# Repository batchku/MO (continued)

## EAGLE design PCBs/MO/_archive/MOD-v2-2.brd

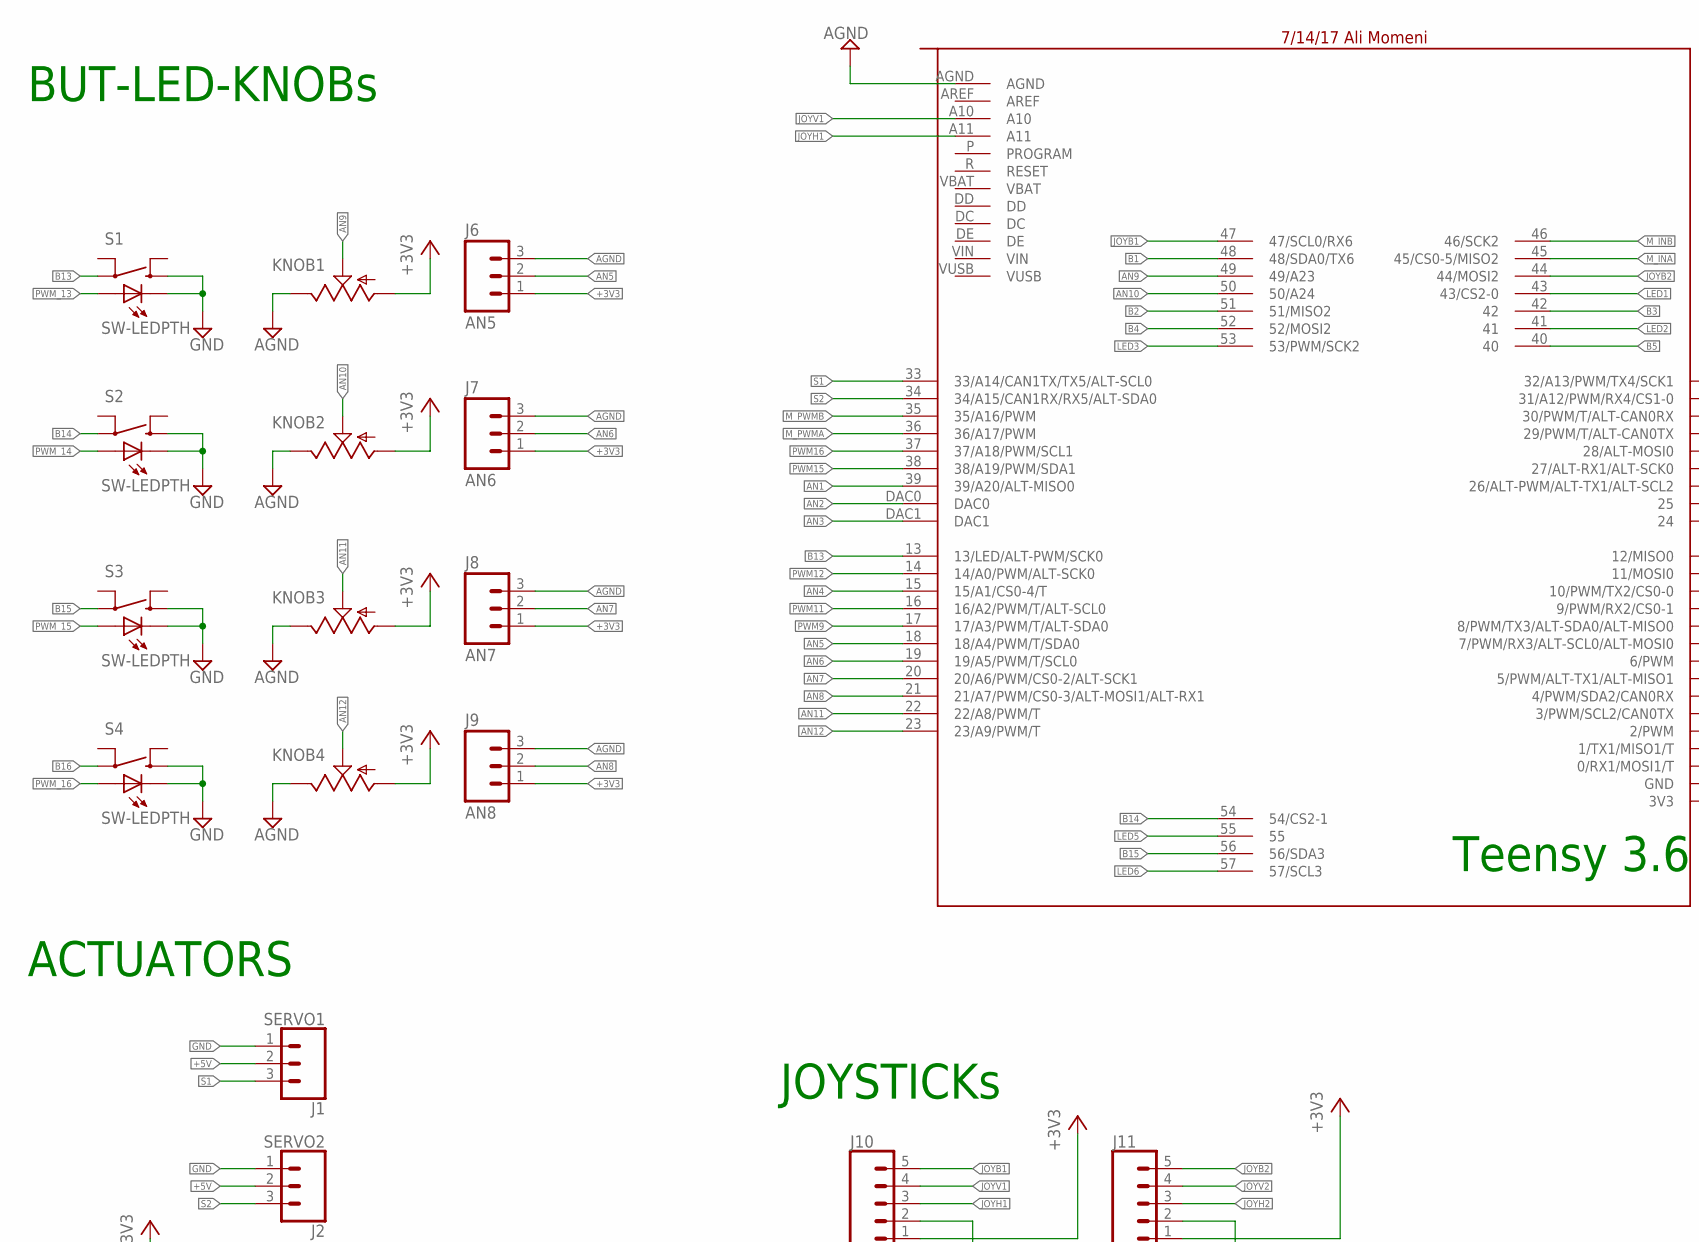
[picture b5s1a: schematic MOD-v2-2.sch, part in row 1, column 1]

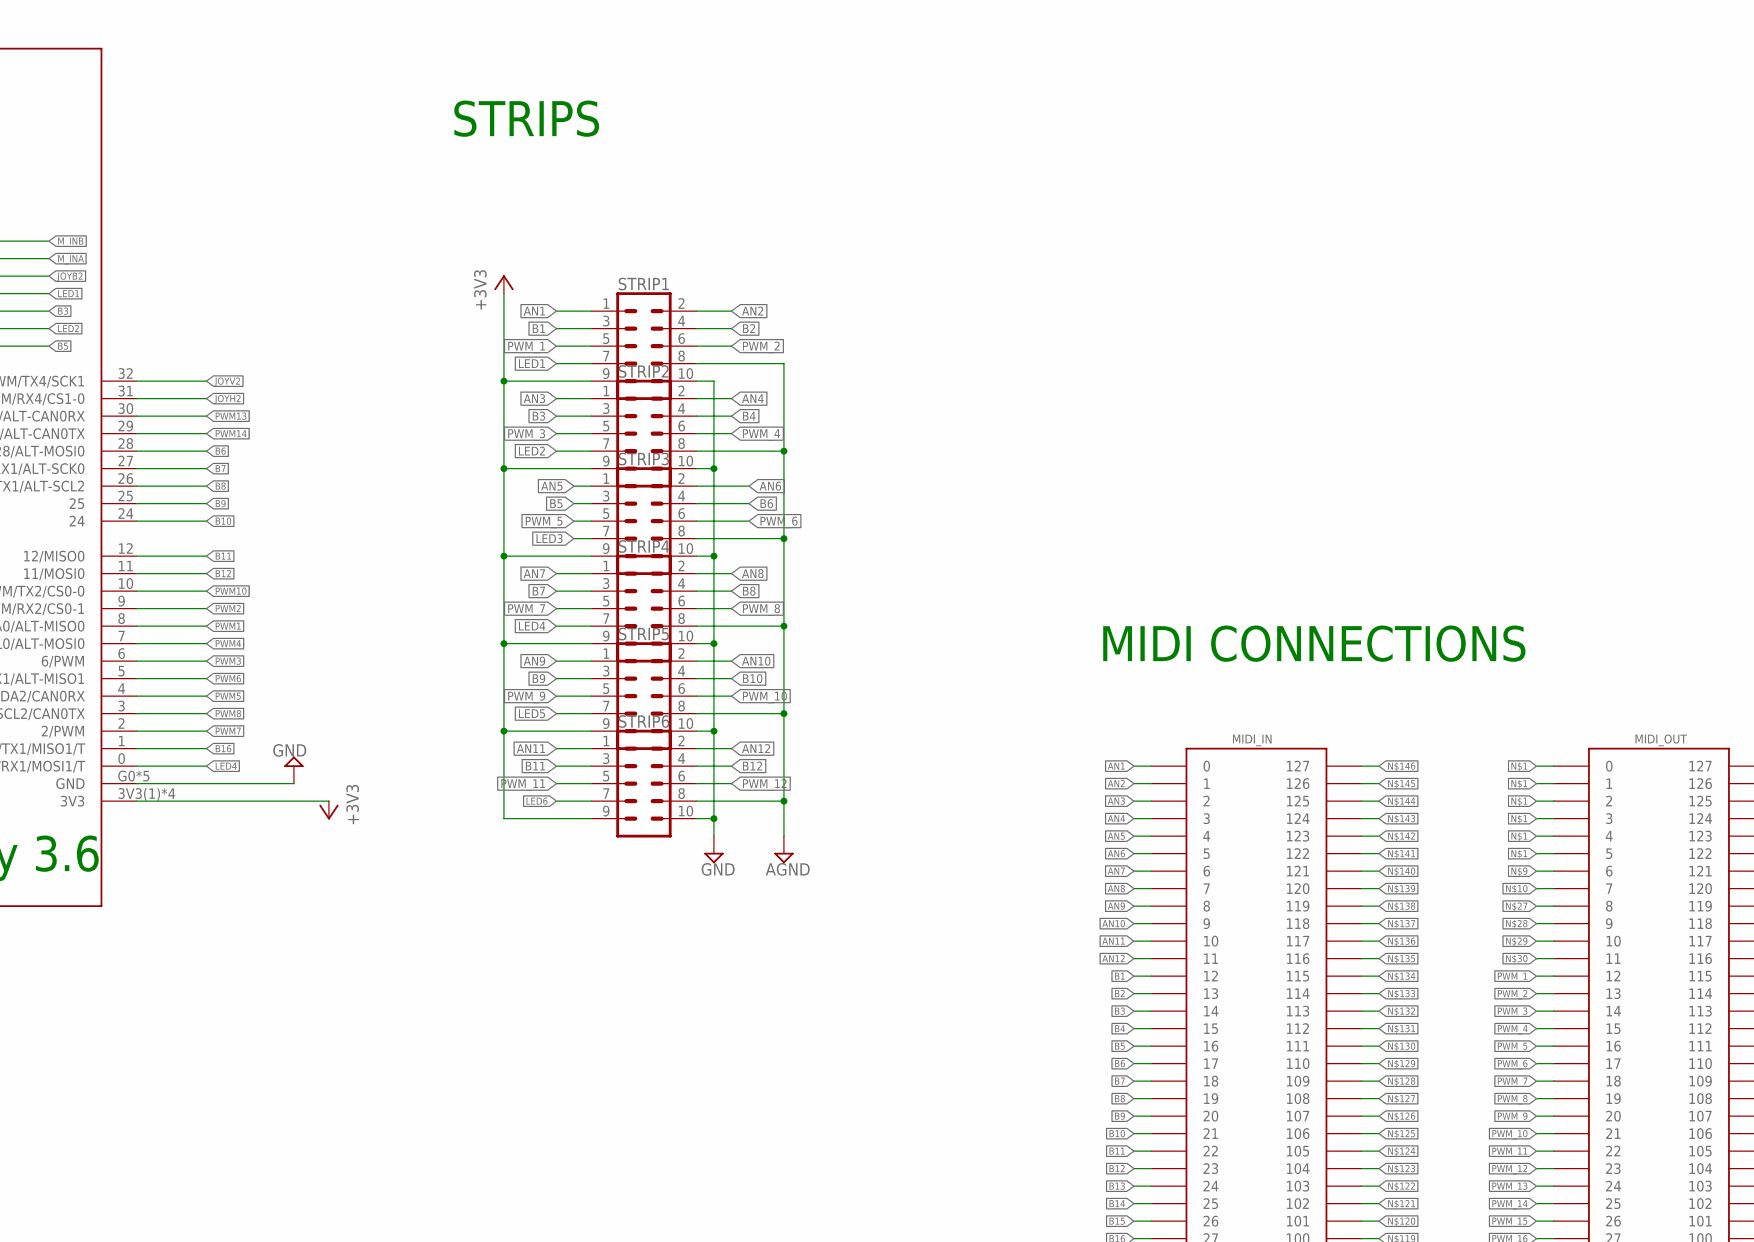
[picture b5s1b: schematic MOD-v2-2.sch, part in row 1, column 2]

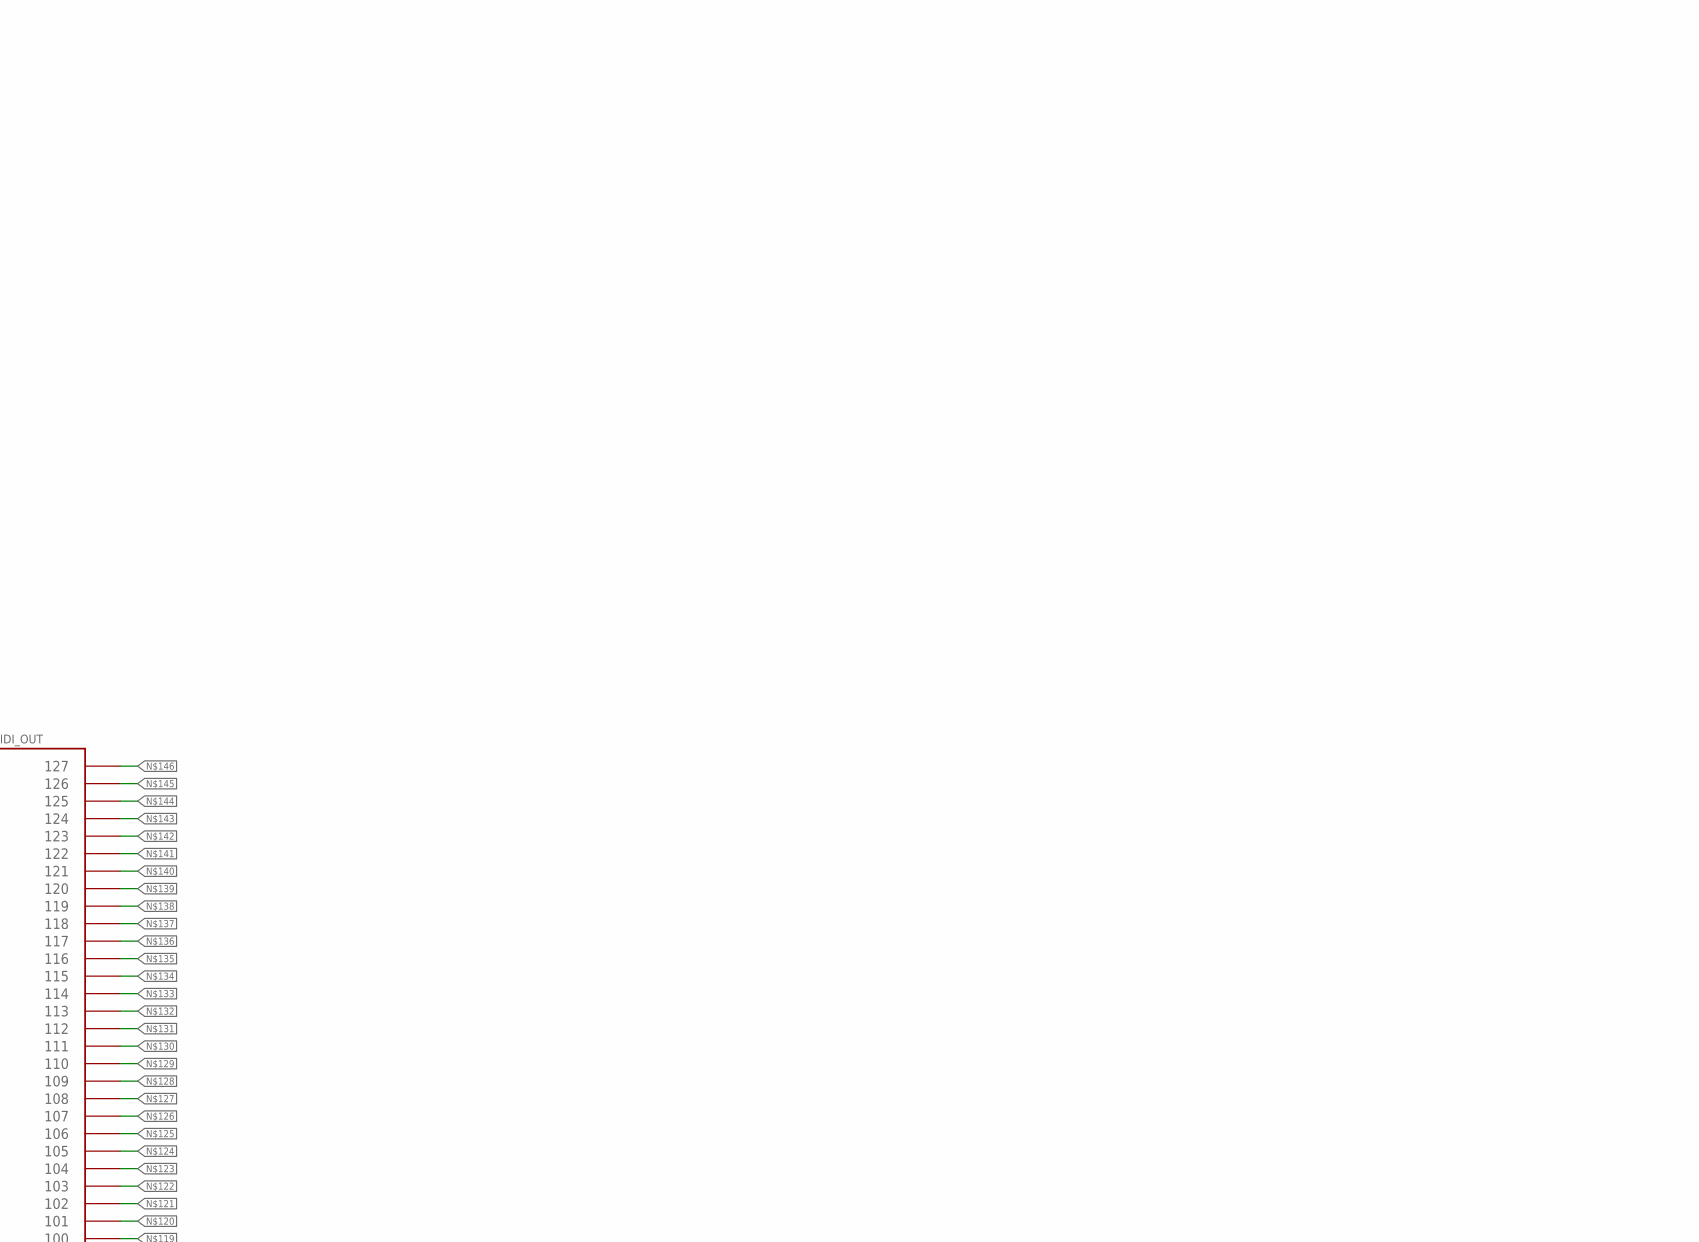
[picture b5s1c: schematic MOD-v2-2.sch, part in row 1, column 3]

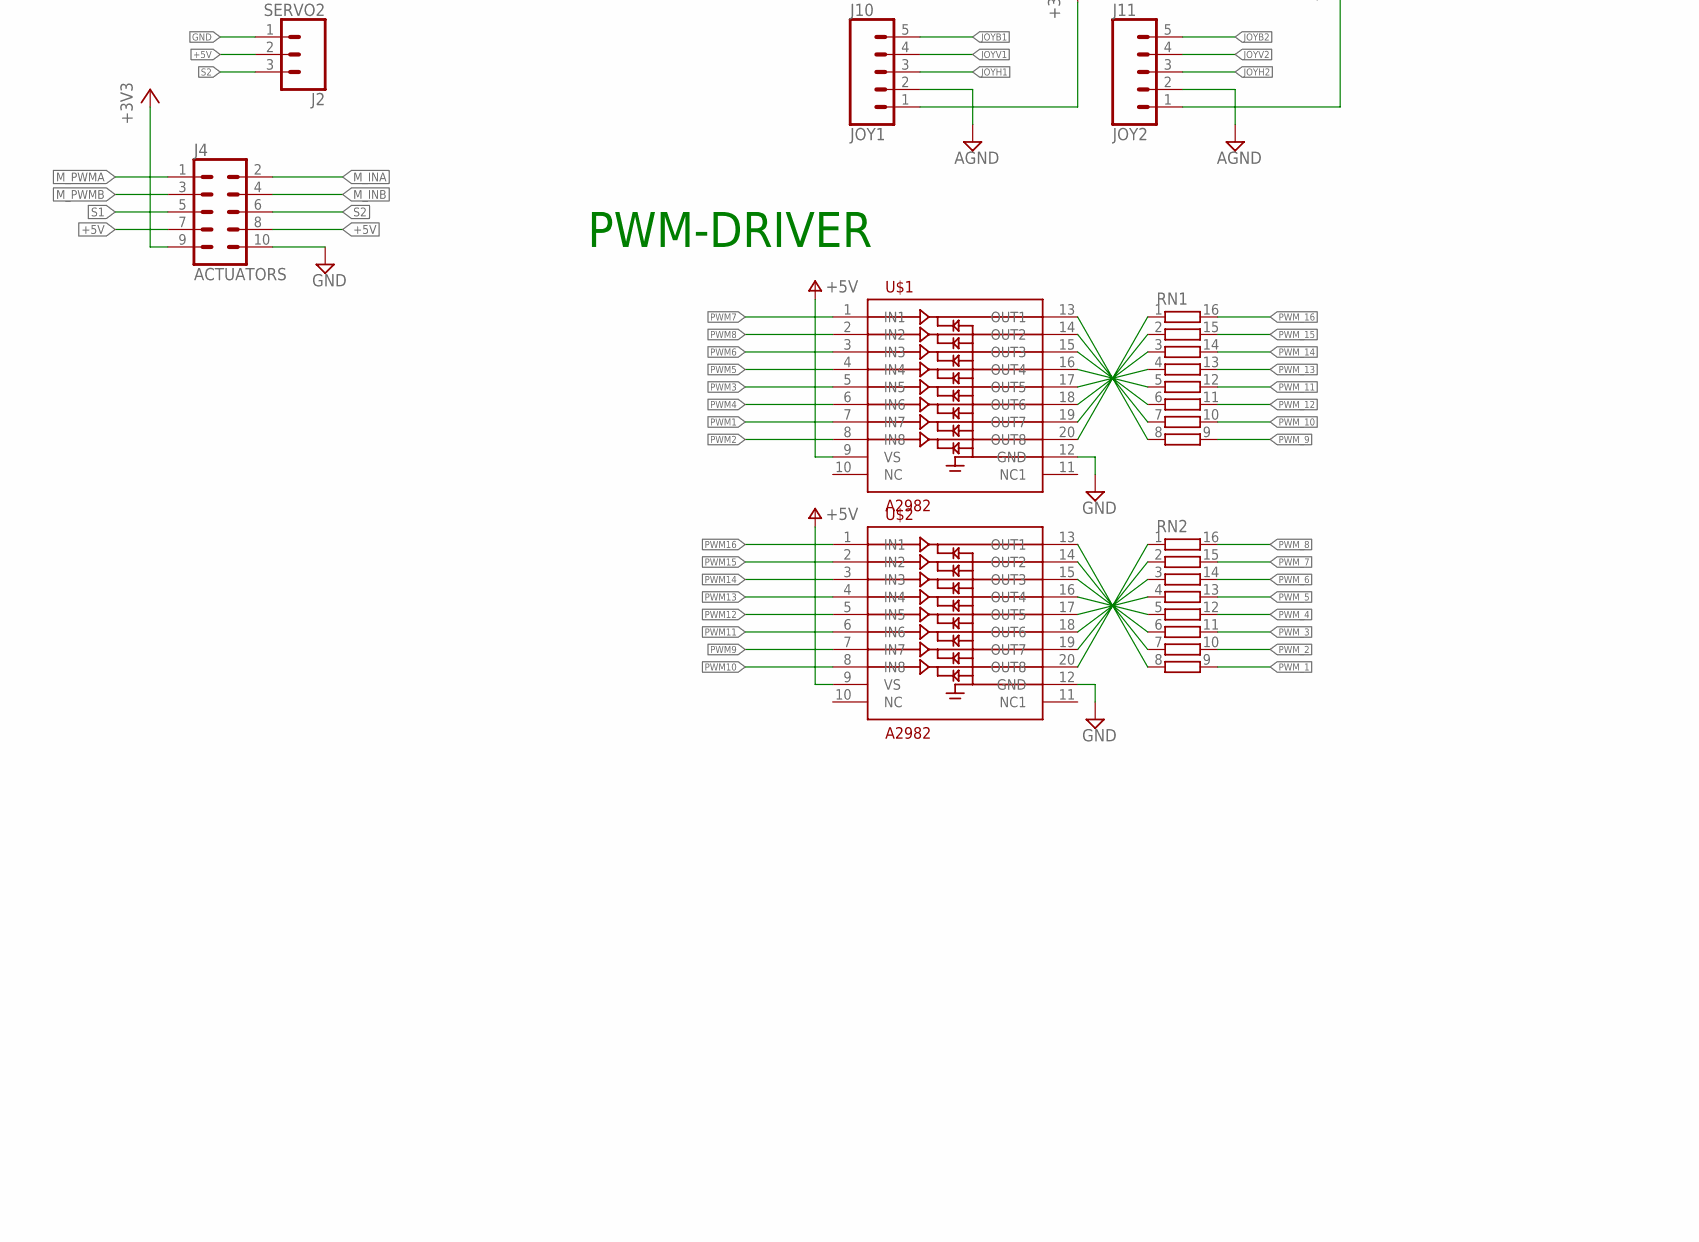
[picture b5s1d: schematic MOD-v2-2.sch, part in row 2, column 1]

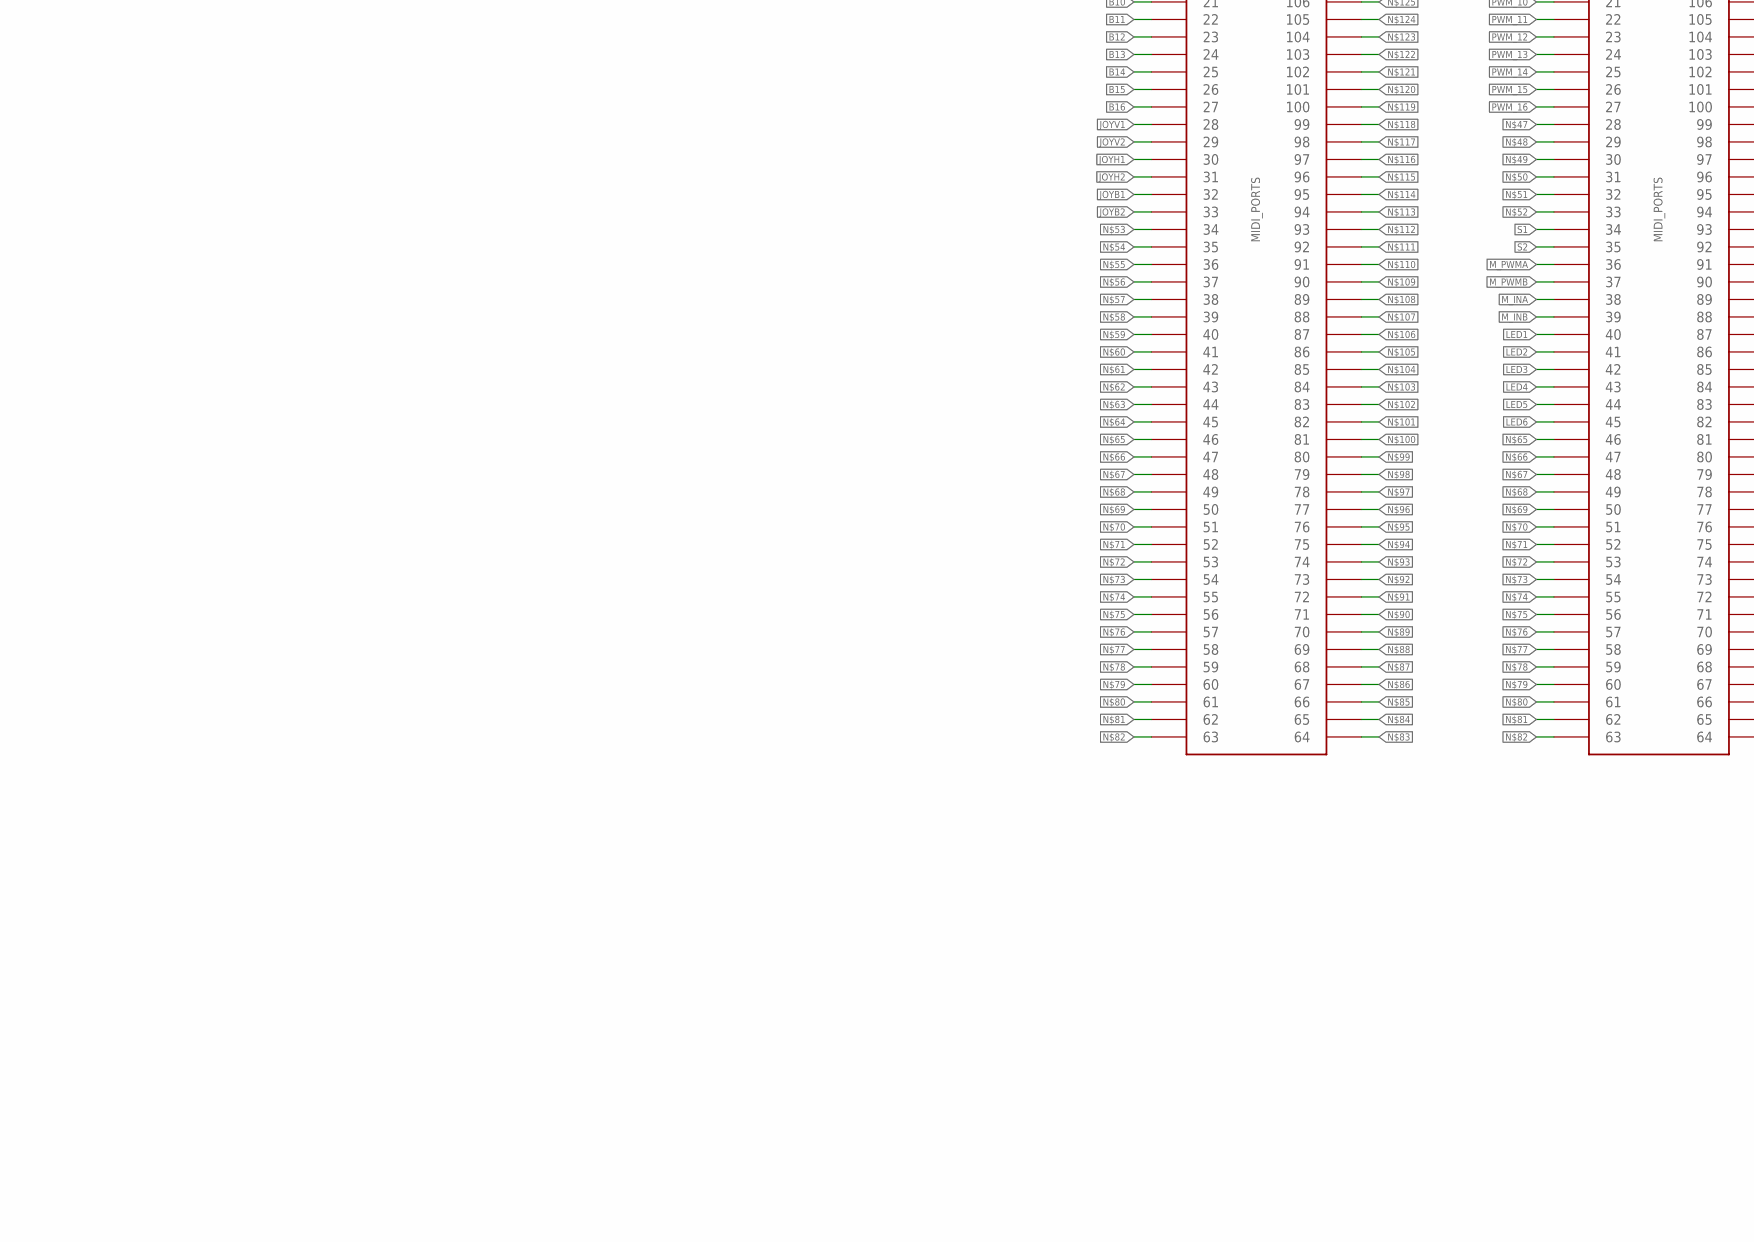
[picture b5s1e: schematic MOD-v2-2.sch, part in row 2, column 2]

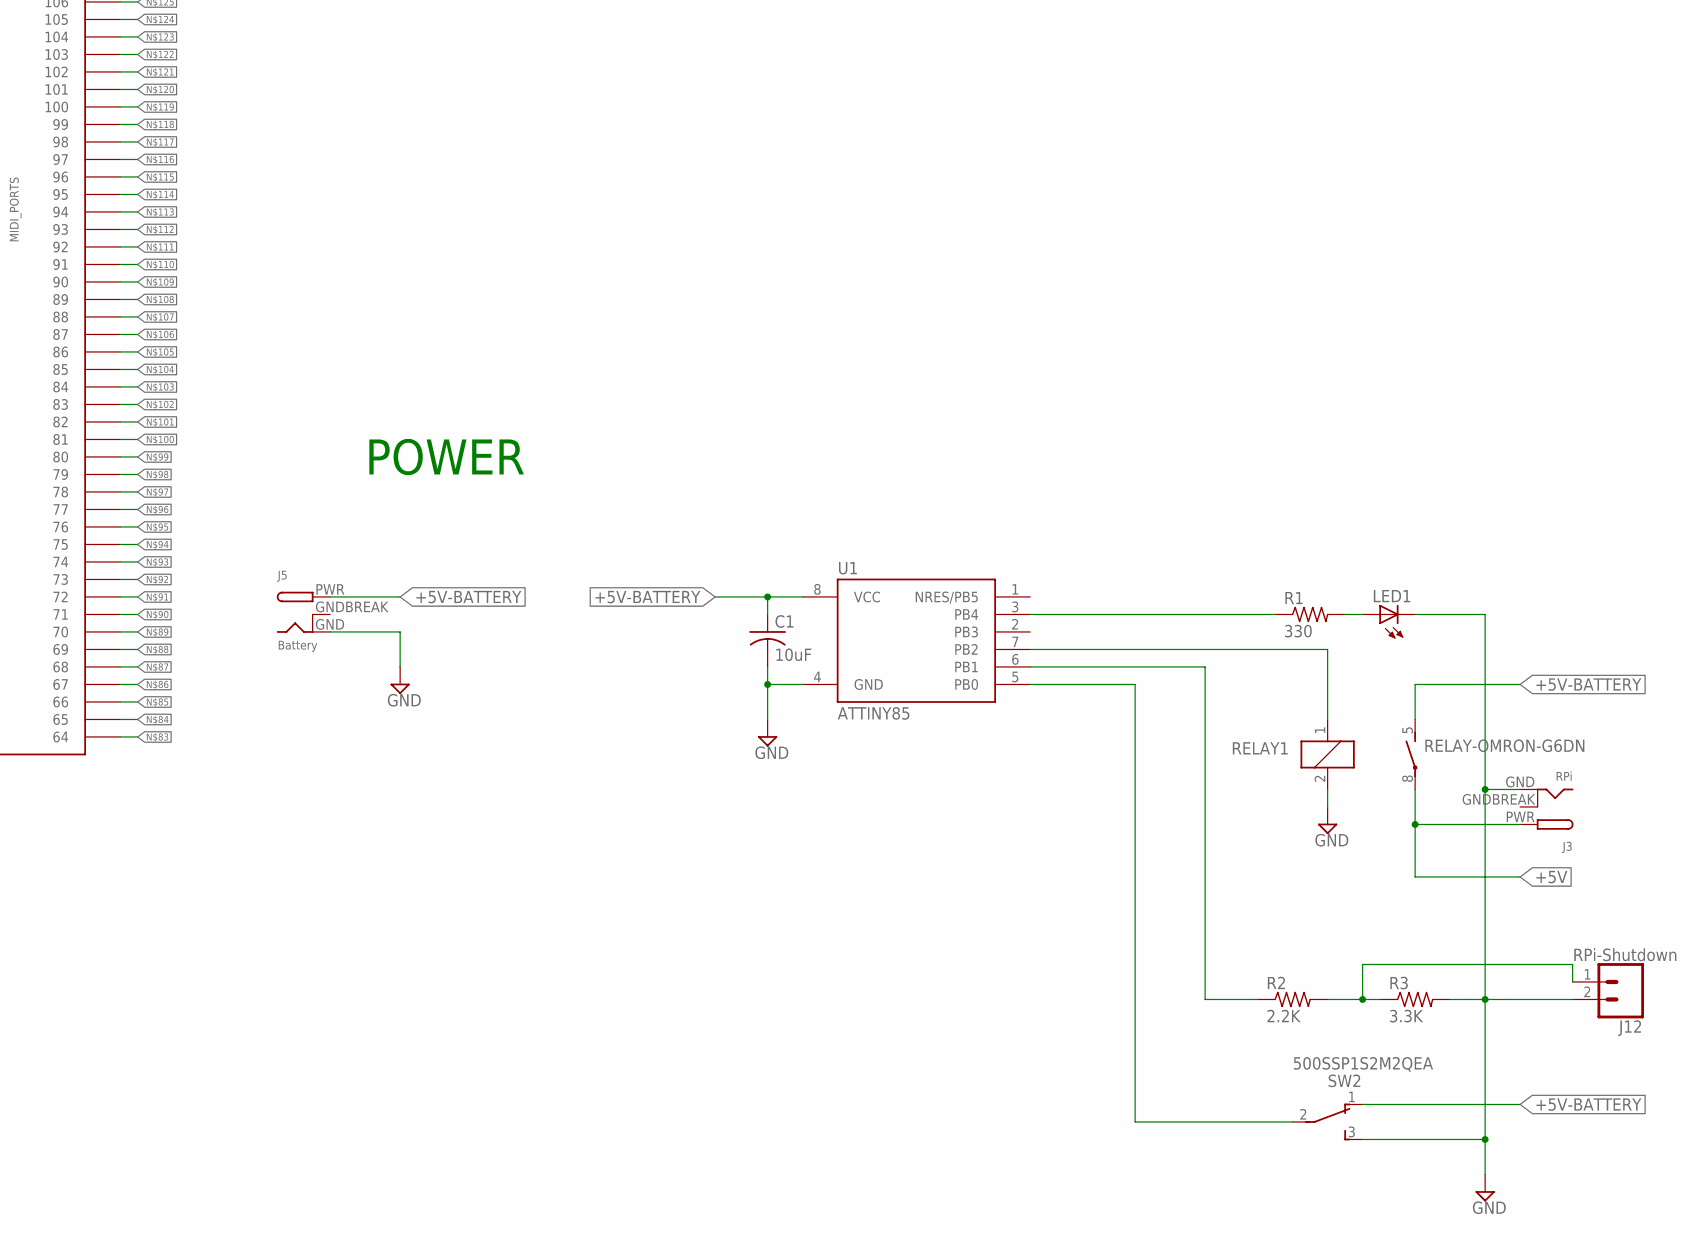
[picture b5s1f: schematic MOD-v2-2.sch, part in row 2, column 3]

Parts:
C1: 10uF; C0805
J1: SERVO1; 1X03_LOCK@1
J2: SERVO2; 1X03_LOCK@1
J3: RPi; DCJACK_2MM_PTH
J4: ACTUATORS; 2X5-SHROUDED_LOCK
J5: Battery; DCJACK_2MM_PTH
J6: AN5; 1X03_LOCK
J7: AN6; 1X03_LOCK
J8: AN7; 1X03_LOCK
J9: AN8; 1X03_LOCK
J10: JOY1; 1X05_LOCK
J11: JOY2; 1X05_LOCK
J12: RPi-Shutdown; 1X02_LOCK
KNOB1, KNOB2, KNOB3, KNOB4: TRIM; TRIM-PCB-9MM
LED1: LED3MM
R1: 330; M0805
R2: 2.2K; M0805
R3: 3.3K; M0805
RELAY1: RELAY-OMRON-G6DN; G6DN-1A
RN1, RN2: 2NBS16-8; SO16
S1, S2, S3, S4: SW-LEDPTH; SWITCH_TR2-MOMENTARY-LED
STRIP1, STRIP2, STRIP3, STRIP4, STRIP5, STRIP6: CONN_05X2SHD_LOCK; 2X5-SHROUDED_LOCK
SW2: 500SSP1S2M2QEA; SWITCH_SPDT_500SSP1S2M2QEA
TEENSY: TEENSY3_6-ALI_NO-USB-HOST; TEENSY3-6_NO-USB-HOST
U1: ATTINY85
U$1, U$2: A2982; SOIC20

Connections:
+3V3: J4.9, J6.1, J7.1, J8.1, J9.1, J10.1, J11.1, KNOB1.1 (A), KNOB2.1 (A), KNOB3.1 (A), KNOB4.1 (A), STRIP1.9, STRIP2.9, STRIP3.9, STRIP4.9, STRIP5.9, STRIP6.9, TEENSY.3V3(1) (3V3), TEENSY.3V3(2) (3V3), TEENSY.3V3(3) (3V3), TEENSY.3V3(4) (3V3)
+5V: J1.2, J2.2, J3.PWR, J4.7, J4.8, R1.1, RELAY1.8, U1.3 (PB4)
+5V-BATTERY: C1.1, J5.PWR, RELAY1.5, SW2.1, U1.8 (VCC)
AGND: J6.3, J7.3, J8.3, J9.3, J10.2, J11.2, KNOB1.3 (E), KNOB2.3 (E), KNOB3.3 (E), KNOB4.3 (E), STRIP1.8, STRIP2.8, STRIP3.8, STRIP4.8, STRIP5.8, STRIP6.8, TEENSY.AGND
AN1: STRIP1.1, TEENSY.39 (39/A20/ALT-MISO0)
AN2: STRIP1.2, TEENSY.DAC0
AN3: STRIP2.1, TEENSY.DAC1
AN4: STRIP2.2, TEENSY.15 (15/A1/CS0-4/T)
AN5: J6.2, STRIP3.1, TEENSY.18 (18/A4/PWM/T/SDA0)
AN6: J7.2, STRIP3.2, TEENSY.19 (19/A5/PWM/T/SCL0)
AN7: J8.2, STRIP4.1, TEENSY.20 (20/A6/PWM/CS0-2/ALT-SCK1)
AN8: J9.2, STRIP4.2, TEENSY.21 (21/A7/PWM/CS0-3/ALT-MOSI1/ALT-RX1)
AN9: KNOB1.2 (S), STRIP5.1, TEENSY.49 (49/A23)
AN10: KNOB2.2 (S), STRIP5.2, TEENSY.50 (50/A24)
AN11: KNOB3.2 (S), STRIP6.1, TEENSY.22 (22/A8/PWM/T)
AN12: KNOB4.2 (S), STRIP6.2, TEENSY.23 (23/A9/PWM/T)
B1: STRIP1.3, TEENSY.48 (48/SDA0/TX6)
B2: STRIP1.4, TEENSY.51 (51/MISO2)
B3: STRIP2.3, TEENSY.42
B4: STRIP2.4, TEENSY.52 (52/MOSI2)
B5: STRIP3.3, TEENSY.40
B6: STRIP3.4, TEENSY.28 (28/ALT-MOSI0)
B7: STRIP4.3, TEENSY.27 (27/ALT-RX1/ALT-SCK0)
B8: STRIP4.4, TEENSY.26 (26/ALT-PWM/ALT-TX1/ALT-SCL2)
B9: STRIP5.3, TEENSY.25
B10: STRIP5.4, TEENSY.24
B11: STRIP6.3, TEENSY.12 (12/MISO0)
B12: STRIP6.4, TEENSY.11 (11/MOSI0)
B13: S1.3, TEENSY.13 (13/LED/ALT-PWM/SCK0)
B14: S2.3, TEENSY.54 (54/CS2-1)
B15: S3.3, TEENSY.56 (56/SDA3)
B16: S4.3, TEENSY.1 (1/TX1/MISO1/T)
GND: C1.2, J1.1, J2.1, J3.GND, J4.10, J5.GND, J12.2, LED1.K (C), R3.2, RELAY1.2, S1.1, S1.C, S2.1, S2.C, S3.1, S3.C, S4.1, S4.C, STRIP1.10, STRIP2.10, STRIP3.10, STRIP4.10, STRIP5.10, STRIP6.10, SW2.3, TEENSY.G0 (GND), TEENSY.G1 (GND), TEENSY.G2 (GND), TEENSY.G3 (GND), TEENSY.G6 (GND), U1.4 (GND), U$1.12 (GND), U$2.12 (GND)
GNDBREAK: J3.GNDBREAK, J5.GNDBREAK
JOYB1: J10.5, TEENSY.47 (47/SCL0/RX6)
JOYB2: J11.5, TEENSY.44 (44/MOSI2)
JOYH1: J10.3, TEENSY.A11
JOYH2: J11.3, TEENSY.31 (31/A12/PWM/RX4/CS1-0)
JOYV1: J10.4, TEENSY.A10
JOYV2: J11.4, TEENSY.32 (32/A13/PWM/TX4/SCK1)
LED1: STRIP1.7, TEENSY.43 (43/CS2-0)
LED2: STRIP2.7, TEENSY.41
LED3: STRIP3.7, TEENSY.53 (53/PWM/SCK2)
LED4: STRIP4.7, TEENSY.0 (0/RX1/MOSI1/T)
LED5: STRIP5.7, TEENSY.55
LED6: STRIP6.7, TEENSY.57 (57/SCL3)
M_INA: J4.2, TEENSY.45 (45/CS0-5/MISO2)
M_INB: J4.4, TEENSY.46 (46/SCK2)
M_PWMA: J4.1, TEENSY.36 (36/A17/PWM)
M_PWMB: J4.3, TEENSY.35 (35/A16/PWM)
unnamed: LED1.A, R1.2
unnamed: SW2.2, U1.5 (PB0)
unnamed: RELAY1.1, U1.7 (PB2)
unnamed: J12.1, R2.2, R3.1
unnamed: RN1.8, U$1.13 (OUT1)
unnamed: RN1.7, U$1.14 (OUT2)
unnamed: RN1.6, U$1.15 (OUT3)
unnamed: RN1.5, U$1.16 (OUT4)
unnamed: RN1.4, U$1.17 (OUT5)
unnamed: RN1.3, U$1.18 (OUT6)
unnamed: RN1.2, U$1.19 (OUT7)
unnamed: RN1.1, U$1.20 (OUT8)
unnamed: RN2.1, U$2.20 (OUT8)
unnamed: RN2.2, U$2.19 (OUT7)
unnamed: RN2.3, U$2.18 (OUT6)
unnamed: RN2.4, U$2.17 (OUT5)
unnamed: RN2.5, U$2.16 (OUT4)
unnamed: RN2.6, U$2.15 (OUT3)
unnamed: RN2.7, U$2.14 (OUT2)
unnamed: RN2.8, U$2.13 (OUT1)
PI-REST: R2.1, U1.6 (PB1)
PWM1: TEENSY.8 (8/PWM/TX3/ALT-SDA0/ALT-MISO0), U$1.7 (IN7)
PWM2: TEENSY.9 (9/PWM/RX2/CS0-1), U$1.8 (IN8)
PWM3: TEENSY.6 (6/PWM), U$1.5 (IN5)
PWM4: TEENSY.7 (7/PWM/RX3/ALT-SCL0/ALT-MOSI0), U$1.6 (IN6)
PWM5: TEENSY.4 (4/PWM/SDA2/CAN0RX), U$1.4 (IN4)
PWM6: TEENSY.5 (5/PWM/ALT-TX1/ALT-MISO1), U$1.3 (IN3)
PWM7: TEENSY.2 (2/PWM), U$1.1 (IN1)
PWM8: TEENSY.3 (3/PWM/SCL2/CAN0TX), U$1.2 (IN2)
PWM9: TEENSY.17 (17/A3/PWM/T/ALT-SDA0), U$2.7 (IN7)
PWM10: TEENSY.10 (10/PWM/TX2/CS0-0), U$2.8 (IN8)
PWM11: TEENSY.16 (16/A2/PWM/T/ALT-SCL0), U$2.6 (IN6)
PWM12: TEENSY.14 (14/A0/PWM/ALT-SCK0), U$2.5 (IN5)
PWM13: TEENSY.30 (30/PWM/T/ALT-CAN0RX), U$2.4 (IN4)
PWM14: TEENSY.29 (29/PWM/T/ALT-CAN0TX), U$2.3 (IN3)
PWM15: TEENSY.38 (38/A19/PWM/SDA1), U$2.2 (IN2)
PWM16: TEENSY.37 (37/A18/PWM/SCL1), U$2.1 (IN1)
PWM_1: RN2.9, STRIP1.5
PWM_2: RN2.10, STRIP1.6
PWM_3: RN2.11, STRIP2.5
PWM_4: RN2.12, STRIP2.6
PWM_5: RN2.13, STRIP3.5
PWM_6: RN2.14, STRIP3.6
PWM_7: RN2.15, STRIP4.5
PWM_8: RN2.16, STRIP4.6
PWM_9: RN1.9, STRIP5.5
PWM_10: RN1.10, STRIP5.6
PWM_11: RN1.12, STRIP6.5
PWM_12: RN1.11, STRIP6.6
PWM_13: RN1.13, S1.A
PWM_14: RN1.14, S2.A
PWM_15: RN1.15, S3.A
PWM_16: RN1.16, S4.A
S1: J1.3, J4.5, TEENSY.33 (33/A14/CAN1TX/TX5/ALT-SCL0)
S2: J2.3, J4.6, TEENSY.34 (34/A15/CAN1RX/RX5/ALT-SDA0)
V+: U$1.9 (VS), U$2.9 (VS)

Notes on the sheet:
BUT-LED-KNOBs
JOYSTICKs
PWM-DRIVER
STRIPS
ACTUATORS
POWER
Teensy 3.6
MIDI CONNECTIONS

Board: 2 copper layers, 39 parts (18 on the bottom side), 106 nets, no tracks yet.

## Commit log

2017-07-26 combining MOM and MOL
2017-07-26 PCB cleanup
2017-07-28 midi lister
2017-07-28 CAD updates big time
2017-07-28 arduino nonsense
2017-07-31 changes to PCBs and CAD for MOL
2017-08-01 daniel tings
2017-08-02 updates to MOL CAD
2017-08-03 changes to MOL cad
2017-08-09 python done
2017-08-09 readme
2017-08-10 clean up
2017-08-10 name changer
2017-08-10 name change from MOL to MOD
2017-08-10 inputs.txt
2017-08-10 pd update
2017-08-11 mo.strip pic
2017-08-15 fixing conflicts
2017-08-17 added RPi power control circuitry
2017-08-17 power control
2017-08-17 attiny added to MOD pcb
2017-08-17 PCB MOD changes
2017-08-17 arduino
2017-08-17 new MOD pcb
2017-08-17 python script added
2017-08-17 routed new MOD pcb v2-2.1
2017-08-18 routed teensy breakout for MOD, v2-2.2.brd
2017-08-18 routed teensy breakout for MOD, v2-2.2.brd updated
2017-08-18 new version of MOD pcb v2-2, under 10cm by 10cm, removes resistor arrays, goes with MOD-strip 2-3
2017-08-18 tweaks to MOD pcb
2017-08-20 new version of MO teensy breakout board, v2-3a
2017-08-20 DRC on MOD pcb v2-3a
2017-08-21 jake suggestions to handle power transmission
2017-08-21 all thru-hole parts, design checked by Jake and Daniel, re-routed with 24mil traces for power
2017-09-11 new MOD teensy board
2017-09-11 update to pinlistet removing N symbols
2017-09-13 arduino refactor
2017-09-15 arduino code working
2017-09-15 removing bad arduino stuff
2017-09-15 removed old MOM arduino stuff from Jesse
2017-09-15 board issues
2017-09-16 new boards
2017-09-16 MOM CAD
2017-09-16 MOD-v2-5 routed
2017-09-16 grasshopper
2017-09-16 new chassis for MOMv2
2017-09-16 names and versions to match
2017-09-16 name changing
2017-09-16 new organization for MOM-v4 pd patches
2017-09-16 mo.init added
2017-09-16 looper patch ready for MOMv4
2017-09-17 adding aLib-pd as submodule
2017-09-17 led flashes for mos
2017-09-17 LED flasher mo.led-flash
2017-09-17 flash
2017-09-17 jesse
2017-09-17 no print
2017-09-17 mixer
2017-09-17 setup added
2017-09-17 loop
2017-09-17 changes to strip MOD and buttom caps
2017-09-17 looper
2017-09-17 collected Pd dependencies into lib folder
2017-09-18 new buttons and caps, now in halves
2017-09-18 more loop
2017-09-18 speed added to ali.looper-pedal
2017-09-18 verb
2017-09-19 re-organized PCB files, changed MOD to MO in PCB file names
2017-09-19 minor change
2017-09-24 new routing for mo-pcb v2-5
2017-09-24 newly routed v2-5 breakout
2017-09-27 re-routed final versions of MO-2.5 and MO-strip-2.5, sent to Fusion
2017-11-23 Pd additions, Arduino Fixes, MO Breakout Cosmetic issues and Midi renaming
2017-11-23 Arduino motor inverse change to digitalWrite
2017-11-25 version 2.5 and 2.6 of MO pcbs both here now
2017-11-27 new amotor board
2017-12-15 new pcb boards and pd patches
2017-12-15 pd fixes
2017-12-15 rm test
2017-12-16 bela project
2017-12-16 bela
2017-12-16 lightbox for bela
2017-12-16 extras removed bela left
2017-12-16 lightrect dxf added
2017-12-16 test
2017-12-16 more tests
2017-12-16 files back
2017-12-16 mo.r and mo.s
2017-12-18 Raspi Power
2017-12-19 pcb and cad changes for mom
2017-12-19 loop update
2017-12-19 looper updates
2017-12-20 almost working looper
2017-12-20 Resonators
2017-12-20 bad object
2017-12-20 res test
2017-12-21 cleanup
2017-12-21 rev3
2017-12-21 new cad modesl for mom
2017-12-22 new clamp for MOM
2017-12-22 last update
2017-12-22 final push
2018-03-02 new Arduino Project
2018-03-02 latest white tickler mom
2018-03-19 MIDI update
2018-03-19 working
2018-03-19 added software PWM
2018-03-19 new pinlist
2018-05-24 QM work
2018-05-25 externals added
2018-05-26 MOM update
2018-05-28 res transform
2018-05-28 Joystick update
2019-04-24 comment lines related to RPi camera
